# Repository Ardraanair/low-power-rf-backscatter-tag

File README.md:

# Low-Power RF Backscatter Tag — KiCad Hardware Design

A portfolio-ready hardware repository for a **low-power RF backscatter tag** designed in KiCad. The repository captures the current PCB/schematic work and documents the intended backscatter architecture, power strategy, RF switching, and next validation steps.

> **Status:** Hardware design / prototype stage. The repository contains the current KiCad source files; RF performance claims should be treated as design targets until validated with laboratory measurements.

## Project at a glance

- **EDA:** KiCad
- **Design title:** `RF_Backscatter_Tag_250_MHz`
- **RF switching:** ADG902BRMZ
- **Logic level translation:** SN74LVC1T45DBV
- **Low-noise regulation:** TPS7A20xxxDBV
- **Antenna interfaces:** two custom antenna-pad symbols/footprints in the supplied schematic
- **Design focus:** low-power load/modulation switching for a compact RF backscatter tag

## Why backscatter?

Backscatter communication avoids generating a complete RF transmit chain on the tag. Instead, the tag changes the RF load presented to an antenna so that an incident RF wave is reflected with different states. This makes the RF front-end substantially simpler than a conventional transmitter.

The reference architecture supplied with this project uses a low-power MCU to acquire sensor data and control timing/modulation, a very-low-power timer to generate a subcarrier, and RF switches to control the reflected signal. The thesis source describes the tag as five functional parts: MCU, timer, watchdog timer, sensor board, and RF front-end. fileciteturn1file3L205-L213

## System architecture

```mermaid
flowchart LR
    P[Low-power power source] --> R[Regulation / power rails]
    R --> MCU[MCU / control logic]
    MCU --> LV[Level translation]
    LV --> SW[RF switch / load modulation]
    ANT1[RF antenna / incident carrier] --> SW
    SW --> ANT2[Reflected / modulated RF]
    MCU --> CTRL[Timing + modulation control]
```

For the thesis reference implementation, the MCU acquires sensor data with a 10-bit ADC and controls the timer and RF front-end; the MCU can enter sleep mode to reduce power. fileciteturn1file0L36-L45

## Current KiCad design

The current schematic in `hardware/Backscatter_tag_First_Version.kicad_sch` is titled **RF_Backscatter_Tag_250_MHz** and includes the following functional elements:

| Ref | Part / function | Role |
|---|---|---|
| U1 | ADG902BRMZ | RF/modulation switch |
| U2 | TPS7A20xxxDBV | Low-power regulator |
| U3 | SN74LVC1T45DBV | Logic-level translation |
| U4, U5 | Custom antenna-pad symbols | RF antenna interfaces |
| C1, C2 | 1 µF | Supply decoupling / stabilization |
| C3 | 100 nF | High-frequency decoupling |
| J1 | 1×4 connector | External interface / programming/test |

### Schematic preview

## Reference timer + RF front-end

The supplied thesis reference shows a timer/RF chain using an **XC6504 voltage reference, TS3002 low-power oscillator, ADG902 modulation switch, and ADG919 RF switch**. The timer generates a 50% duty-cycle subcarrier and the MCU controls the modulation switch. fileciteturn1file1L98-L113

The reference prototype programmed the timer to **34.3 kHz** and reported **2.62 µW** for the timer circuit including the voltage reference. These are reference-design measurements, not measurements of the current KiCad board in this repository. fileciteturn1file1L109-L113

## Reference system-level concept

The supplied reference material describes ambient/backscatter systems in which an incident RF/FM signal is reflected and modulated by the tag, with a low-cost SDR used at the receiver. fileciteturn0file0L547-L560

## Design principles demonstrated

### 1. RF load modulation

The core idea is to switch the electrical state seen by the antenna so that the reflection coefficient changes. In a backscatter system, the incident carrier supplies the RF energy and the tag encodes information through controlled reflection states. fileciteturn1file2L130-L145

### 2. Ultra-low-power timing

The reference design uses a low-power oscillator to create the tag subcarrier and an MCU-controlled switch to gate/modulate it. fileciteturn1file0L46-L56

### 3. Duty-cycled operation

The reference system uses a nano-power watchdog timer to wake the MCU periodically, allowing the processor and RF circuitry to remain off for most of the time. The cited implementation used a TPL5010 and a 4-second wake interval. fileciteturn1file9L426-L438

### 4. Simple modulation

The reference implementation uses OOK with Morse encoding for a deliberately simple, low-complexity link. The MCU creates the baseband timing while the external timer defines the subcarrier frequency. fileciteturn1file3L166-L183

## Repository structure

```text
.
├── README.md
├── .gitignore
├── hardware/
│   ├── Backscatter_Tag_First_Version.kicad_pro
│   ├── Backscatter_tag_First_Version.kicad_sch
│   ├── Backscatter_Tag_First_Version.kicad_pcb
│   └── README.md
├── manufacturing/
│   └── Tag-odb.zip
├── docs/
│   ├── ARCHITECTURE.md
│   ├── PORTFOLIO.md
│   ├── VALIDATION.md
│   └── images/
│       └── kicad-schematic.png
├── firmware/
├── simulation/
└── scripts/
    └── check_repo.sh
```

## How to open the design

1. Install KiCad 10.x.
2. Clone this repository.
3. Open `hardware/Backscatter_Tag_First_Version.kicad_pro`.
4. Inspect the schematic first, then open the PCB editor.
5. Before fabrication, run ERC/DRC and verify the RF path, supply rails, connector pinout, antenna geometry, and footprints against the exact manufacturer datasheets.

### Important reproducibility note

The supplied schematic references custom antenna symbols/footprints (`My_custom_symbols_1:Ant_smd_RF1` and `my_custom_footprints:Antenna_Pad`). The uploaded source archive did not contain the corresponding custom library files. If KiCad reports missing libraries, restore those custom libraries and update `sym-lib-table` / `fp-lib-table` before editing or manufacturing.

## Suggested next engineering steps

- Add the missing custom symbol/footprint libraries and lock library versions.
- Add the MCU, timer, watchdog, sensor and complete power tree if this repository is intended to reproduce the full reference tag rather than only the current RF board.
- Add an RF matching/load network and document the intended antenna impedance.
- Add ERC/DRC reports to `docs/validation/`.
- Add a generated BOM and component datasheet links.
- Add measured VNA/S11 data and RF-switch insertion-loss/isolation results.
- Add oscilloscope captures showing the modulation waveform.
- Add a receiver-side SDR/MATLAB or Python decoder if the complete communication chain is implemented.
- Add manufacturing outputs only after the final PCB revision has passed DRC and fabrication checks.

## Validation roadmap

| Test | Instrument | Evidence to add |
|---|---|---|
| Power-rail verification | DMM / oscilloscope | Rail voltage + current table |
| RF switch control | Oscilloscope | Control waveform |
| S11 / antenna matching | VNA | Touchstone `.s1p` + plot |
| RF insertion loss / isolation | VNA | Measurement table |
| Backscatter waveform | SDR / spectrum analyzer | IQ capture + spectrum |
| End-to-end link | SDR receiver | BER/PER vs distance |
| Power consumption | SMU / source meter | Active/sleep current |

## Reference performance context

The supplied thesis reports a proof-of-concept backscatter tag using a low-power MCU, external timer and RF front-end; its prototype consumed around **20 µW** and achieved indoor communication up to **2 m** in the described experiment. fileciteturn0file0L587-L602

Those numbers belong to the reference implementation and should **not** be presented as measured results for this repository unless independently reproduced.

## Portfolio / resume value

This project demonstrates:

- KiCad schematic capture and PCB design
- RF switch/load-modulation concepts
- low-power electronics
- power-rail and decoupling design
- digital/RF interface considerations
- antenna-interface design
- hardware documentation and reproducibility
- a clear path from schematic → PCB → RF characterization → wireless validation

## Attribution

The backscatter architecture and technical context documented here were informed by the supplied thesis *Ambient Backscatterers For Low Cost and Low Power Wireless Applications* by Spyridon Nektarios Daskalakis, Heriot-Watt University, 2020. fileciteturn0file0L2-L10

The KiCad files in `hardware/` are the current project files supplied for this portfolio repository.

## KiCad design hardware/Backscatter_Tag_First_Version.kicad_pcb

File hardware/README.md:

# Hardware Source

This directory contains the supplied KiCad project files for the current RF backscatter tag design.

| File | Purpose |
|---|---|
| `Backscatter_Tag_First_Version.kicad_pro` | KiCad project configuration |
| `Backscatter_tag_First_Version.kicad_sch` | Schematic source |
| `Backscatter_Tag_First_Version.kicad_pcb` | PCB layout source |

The schematic title is `RF_Backscatter_Tag_250_MHz`.

## Before editing

The schematic references custom antenna libraries:

- `My_custom_symbols_1:Ant_smd_RF1`
- `my_custom_footprints:Antenna_Pad`

The supplied archive did not contain those library files. Add them to the project and configure `sym-lib-table` / `fp-lib-table` before making a manufacturing revision.

## Manufacturing archive

The supplied ODB archive is stored separately under `../manufacturing/` so that source design files and manufacturing artifacts remain clearly separated.

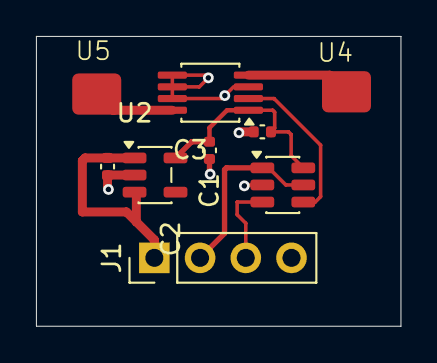
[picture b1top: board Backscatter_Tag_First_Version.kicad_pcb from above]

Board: 2 copper layers, 20.2 x 16.1 mm, 9 parts (0 on the bottom side), 8 nets.

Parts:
C1, C2: 1 uF; C_0402_1005Metric
C3: 100 nF; C_0402_1005Metric
J1: Conn_01x04; PinHeader_1x04_P2.54mm_Vertical
U1: ADG902BRMZ; MSOP-8_3x3mm_P0.65mm
U2: TPS7A20xxxDBV; SOT-23-5
U3: SN74LVC1T45DBV; SOT-23-6
U4, U5: Antenna_Pad

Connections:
2.5 V: C1.1, C3.2, U1.1 (VDD), U2.5 (OUT), U3.6 (VCCB)
3.3 V: J1.2, U3.1 (VCCA), U3.5 (DIR)
+5V: C2.1, J1.1, U2.1 (IN), U2.3 (EN)
GND: C1.2, C2.2, C3.1, J1.4, U1.3 (GND), U1.5 (GND), U1.6 (GND), U1.7 (GND), U2.2 (GND), U3.2 (GND)
unnamed: J1.3, U3.3 (A)
unnamed: U1.2 (CTRL), U3.4 (B)
unnamed: U1.4 (RF1), U4.1 (A+_1)
unnamed: U1.8 (RF2), U5.1 (A+_1)
